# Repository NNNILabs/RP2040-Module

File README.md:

# RP2040 Module
## Introduction
A small-footprint RP2040 breakout board, with additional features like extended memory and a fast optically-isolated interface. 
## Project Motivation
Two projects of mine, a [breakout board](https://github.com/NNNILabs/AD4630-Wideband-Digital-LNA) investigating the AD4630 and a [modular power supply](https://github.com/diminDDL/TripleChannelPSU), both needed a compact RP2040 breakout board. Since they needed some shared features, I decided to make one board to use with both (and possibly more) projects.
## Usage
[under construction]
## List of Files
- Hardware: KiCAD PCB files, 3D models

- Resources: Pinout diagram
## Application Examples
[under construction]
## Notes
- Projects like the [RP2040 Stamp](https://shop.pimoroni.com/products/rp2040-stamp?variant=39567567028307) and the [RP2040 ISP Stamp](https://www.osborneee.com/rp2040-isp-stamp/) exist, but they lack some of the features I need and modifying the files was very difficult because of sketchy layout. I decided I could do better in the latter aspect. 
## Links
[under construction]

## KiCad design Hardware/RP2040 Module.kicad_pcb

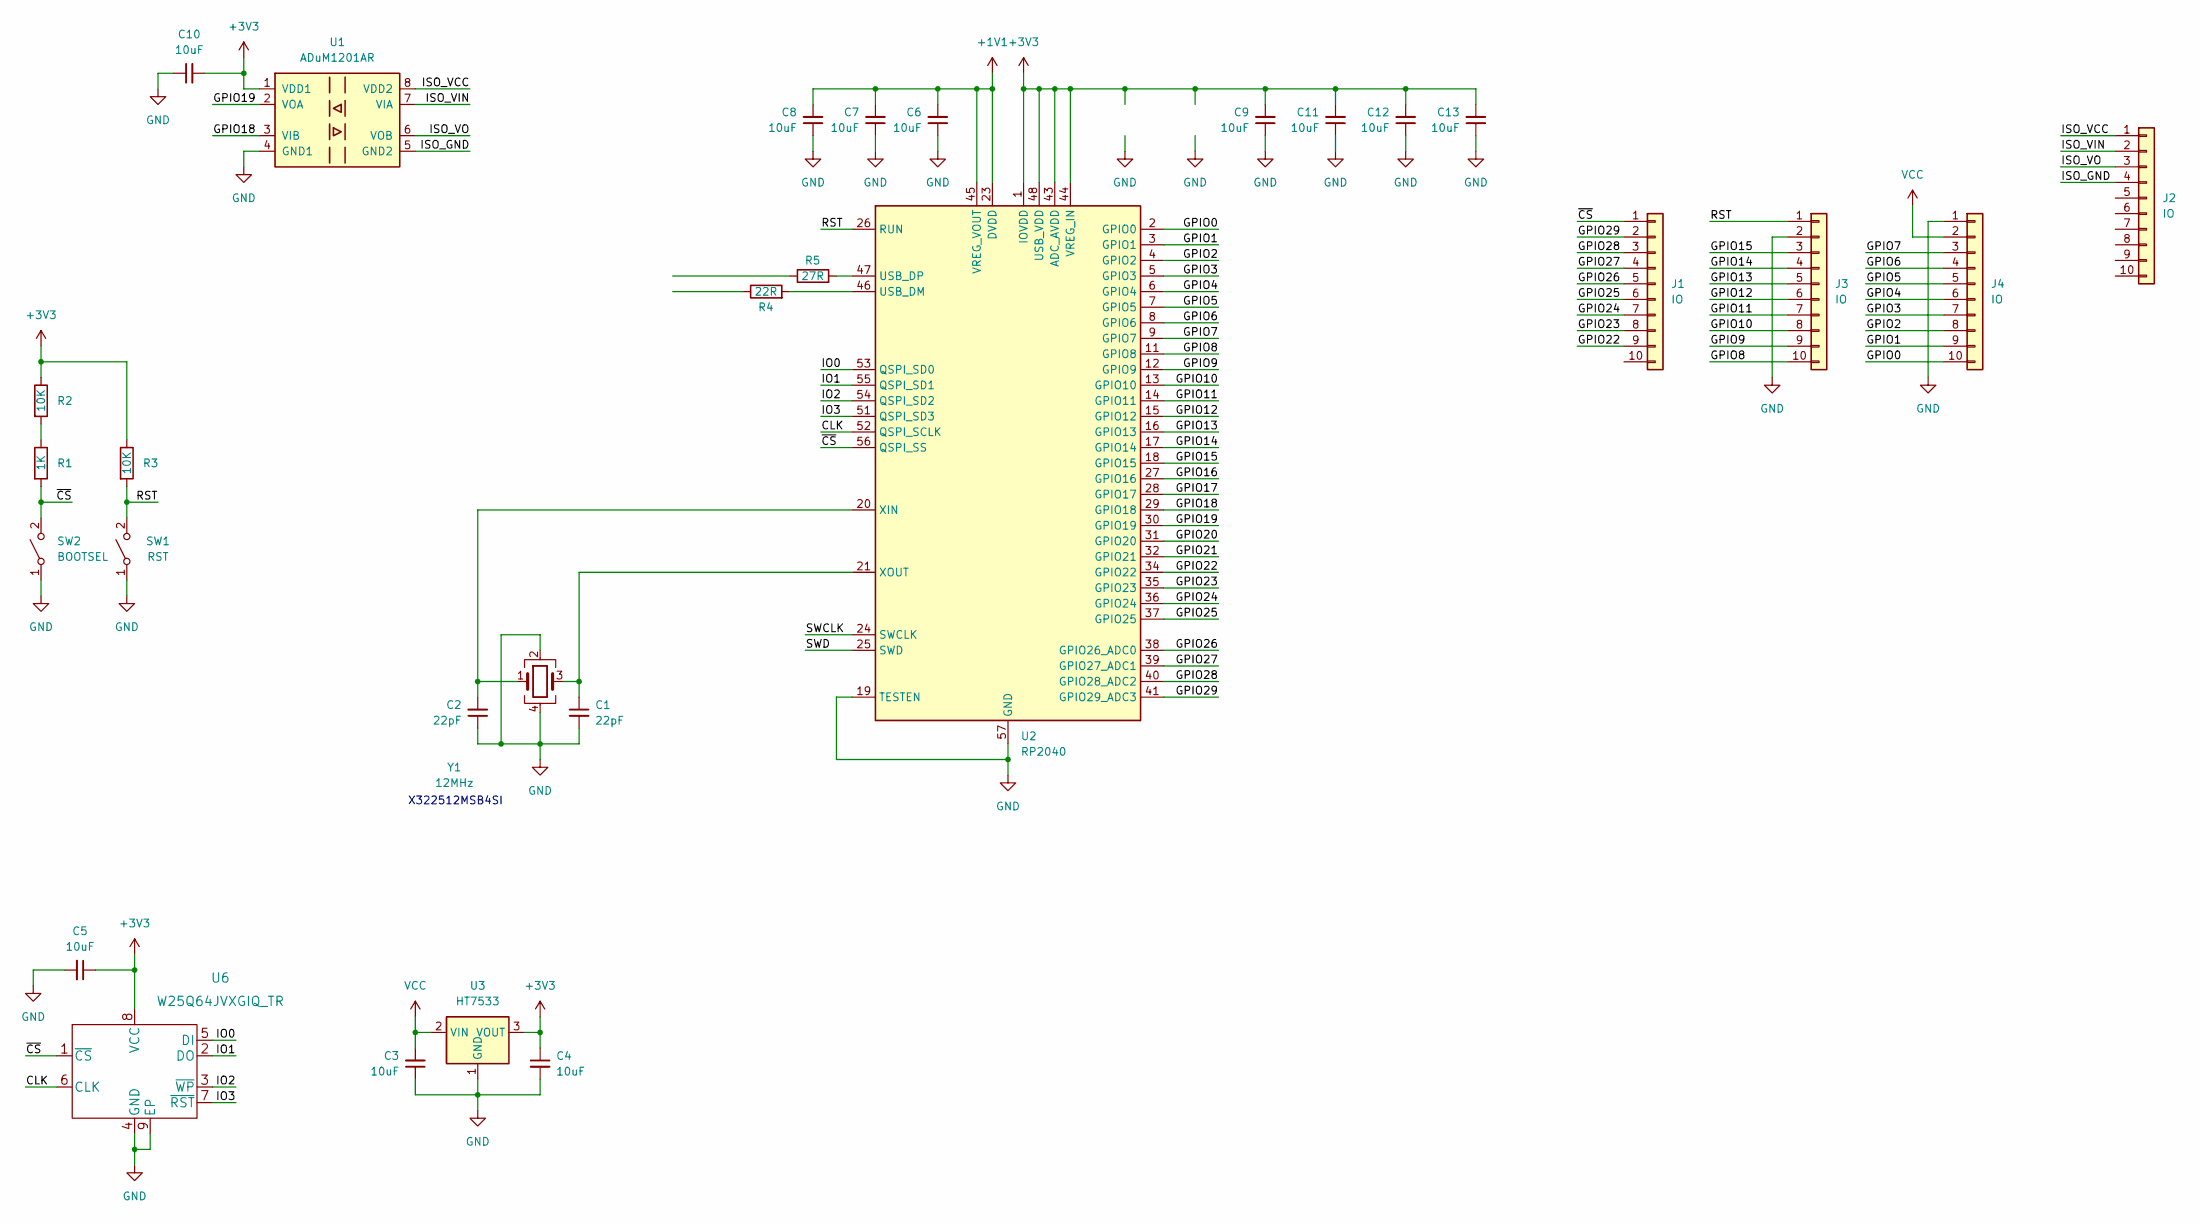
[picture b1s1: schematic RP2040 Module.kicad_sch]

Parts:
C1, C2: 22pF; C_0402_1005Metric
C3, C4, C5, C6, C7, C8, C9, C10, C11, C12, C13: 10uF; C_0402_1005Metric
J1, J2, J3, J4: IO; PinHeader_1x10_P2.00mm_Vertical
R1: 1K; R_0402_1005Metric
R2, R3: 10K; R_0402_1005Metric
R4: 22R; R_0402_1005Metric
R5: 27R; R_0402_1005Metric
SW1: RST; SW_SPST_B3U-1000P
SW2: BOOTSEL; SW_SPST_B3U-1000P
U1: ADuM1201AR; SOIC-8_3.9x4.9mm_P1.27mm
U2: RP2040; QFN-56-1EP_7x7mm_P0.4mm_EP3.2x3.2mm
U3: HT7533; SOT-89-3
U6: W25Q64JVXGIQ_TR; W25Q64JVXGIQ TR
Y1: 12MHz; Oscillator_SMD_Abracon_ASE-4Pin_3.2x2.5mm

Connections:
+1V1: C6.2, C7.2, C8.2, U2.23 (DVDD), U2.45 (VREG_VOUT), U2.50 (DVDD)
+3V3: C4.1, C5.1, C9.2, C10.2, C11.2, C12.2, C13.2, R2.1, R3.1, U1.1 (VDD1), U2.1 (IOVDD), U2.10 (IOVDD), U2.22 (IOVDD), U2.33 (IOVDD), U2.42 (IOVDD), U2.43 (ADC_AVDD), U2.44 (VREG_IN), U2.48 (USB_VDD), U2.49 (IOVDD), U3.3 (VOUT), U6.8 (VCC)
/CLK: U2.52 (QSPI_SCLK), U6.6 (CLK)
/GPIO0: J4.10, U2.2 (GPIO0)
/GPIO1: J4.9, U2.3 (GPIO1)
/GPIO2: J4.8, U2.4 (GPIO2)
/GPIO3: J4.7, U2.5 (GPIO3)
/GPIO4: J4.6, U2.6 (GPIO4)
/GPIO5: J4.5, U2.7 (GPIO5)
/GPIO6: J4.4, U2.8 (GPIO6)
/GPIO7: J4.3, U2.9 (GPIO7)
/GPIO8: J3.10, U2.11 (GPIO8)
/GPIO9: J3.9, U2.12 (GPIO9)
/GPIO10: J3.8, U2.13 (GPIO10)
/GPIO11: J3.7, U2.14 (GPIO11)
/GPIO12: J3.6, U2.15 (GPIO12)
/GPIO13: J3.5, U2.16 (GPIO13)
/GPIO14: J3.4, U2.17 (GPIO14)
/GPIO15: J3.3, U2.18 (GPIO15)
/GPIO16: U2.27 (GPIO16)
/GPIO17: U2.28 (GPIO17)
/GPIO18: U1.3 (VIB), U2.29 (GPIO18)
/GPIO19: U1.2 (VOA), U2.30 (GPIO19)
/GPIO20: U2.31 (GPIO20)
/GPIO21: U2.32 (GPIO21)
/GPIO22: J1.9, U2.34 (GPIO22)
/GPIO23: J1.8, U2.35 (GPIO23)
/GPIO24: J1.7, U2.36 (GPIO24)
/GPIO25: J1.6, U2.37 (GPIO25)
/GPIO26: J1.5, U2.38 (GPIO26_ADC0)
/GPIO27: J1.4, U2.39 (GPIO27_ADC1)
/GPIO28: J1.3, U2.40 (GPIO28_ADC2)
/GPIO29: J1.2, U2.41 (GPIO29_ADC3)
/IO0: U2.53 (QSPI_SD0), U6.5 (DI)
/IO1: U2.55 (QSPI_SD1), U6.2 (DO)
/IO2: U2.54 (QSPI_SD2), U6.3 (~WP)
/IO3: U2.51 (QSPI_SD3), U6.7 (~RST)
/ISO_GND: J2.4, U1.5 (GND2)
/ISO_VCC: J2.1, U1.8 (VDD2)
/ISO_VIN: J2.2, U1.7 (VIA)
/ISO_VO: J2.3, U1.6 (VOB)
/RST: J3.1, R3.2, SW1.2 (B), U2.26 (RUN)
/SWCLK: U2.24 (SWCLK)
/SWD: U2.25 (SWD)
/~CS: J1.1, R1.2, SW2.2 (B), U2.56 (QSPI_SS), U6.1 (~CS)
GND: C1.2, C2.1, C3.1, C4.2, C5.2, C6.1, C7.1, C8.1, C9.1, C10.1, C11.1, C12.1, C13.1, J3.2, J4.1, SW1.1 (A), SW2.1 (A), U1.4 (GND1), U2.19 (TESTEN), U2.57 (GND), U3.1 (GND), U6.4 (GND), U6.9 (EP), Y1.2, Y1.4
unnamed: R1.1, R2.2
unnamed: R4.2, U2.46 (USB_DM)
unnamed: R5.2, U2.47 (USB_DP)
unnamed: C2.2, U2.20 (XIN), Y1.1
unnamed: C1.1, U2.21 (XOUT), Y1.3
VCC: C3.2, J4.2, U3.2 (VIN)

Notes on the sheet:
X322512MSB4SI

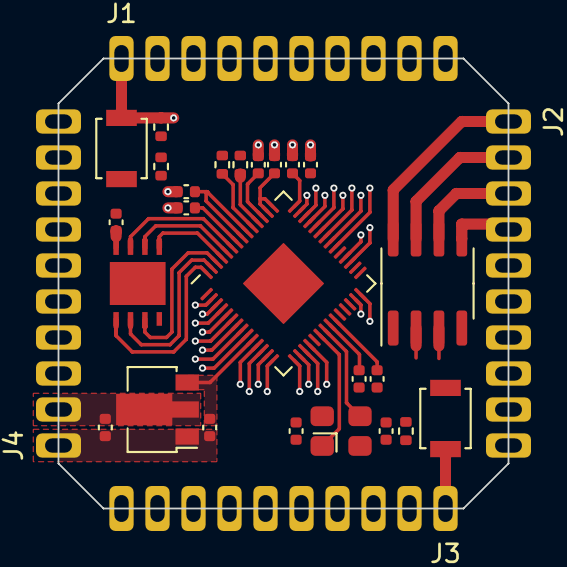
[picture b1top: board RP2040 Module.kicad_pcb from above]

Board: 4 copper layers, 25.0 x 25.0 mm, 29 parts (0 on the bottom side), 46 nets.

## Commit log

2023-01-20 updated files
2024-01-27 sync update
